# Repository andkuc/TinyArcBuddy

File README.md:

# Tiny Arc Buddy: Embedded STEM Education Platform

An open-source, ATtiny85-based handheld console designed as a dual-purpose platform: a low-level embedded engineering reference and a hands-on STEM educational tool. It is based on the ATtiny85 Tiny Arcade Console by lonesoulsurfer (https://www.instructables.com/Tiny-Arcade-Game-Attiny85).

Developed for STEM workshops, this project aims to demystify hardware assembly and firmware development for 8th-grade middle school students.

---

## 🧠 Pedagogical Approach

The Tiny Arc Buddy is engineered to provide a frictionless, high-impact introduction to STEM for young students without requiring prior programming or electronics experience.

* **Peer-to-Peer Mentoring:** The workshop utilizes a tiered mentoring model. Middle school students act as "Lead Engineers" executing the hands-on work, while older HTL students serve as "Senior Advisors," fostering a collaborative, non-intimidating learning environment.
* **Tangible Milestones:** Hardware assembly is gamified into structural "Levels" (low-profile to high-profile components). This prevents cognitive overload and provides continuous positive reinforcement.
* **Immediate Feedback Loop:** The firmware is structured with a dedicated `ZONE 1: APP SETTINGS`. Students modify straightforward C++ macros (e.g., `#define OWNER_NAME "ANNA"`) and immediately see their changes compiled and rendered on the OLED. This bridges the abstract code-to-hardware gap without bogging them down in syntax errors.
* **Curriculum Alignment:** The software payloads (such as the Affine Linear Function Explorer) directly correlate with the Austrian 8th-grade mathematics and physics curricula, demonstrating the practical application of theoretical school concepts.

---

## ⚡ Hardware Architecture

| **Front Board Layout** | **Schematic Diagram** |
| :---: | :---: |
|  |  |

The hardware is designed around strict BOM constraints, prioritizing low cost, through-hole technology (THT) for beginner soldering, and extreme power efficiency.

* **MCU:** Microchip ATtiny85-20PU (8 KB Flash, 512 Bytes SRAM).
* **Clock:** 8 MHz Internal Oscillator (Fuses must be set; factory 1 MHz will fail I2C timings).
* **Display:** 0.96" I²C SSD1306 Monochrome OLED ($128 \times 64$).
* **Inputs:** * `BTN_LEFT` (PB0) - Direct digital read with internal pull-up.
  * `BTN_RIGHT` (PB2) - Direct digital read with internal pull-up.
  * `BTN_FIRE` (PB5 / ADC0) - Multiplexed via voltage divider (Reset pin constraint).
* **Audio:** Passive Piezo Buzzer driven by PB1.
* **Power:** 3V CR2032 Coin Cell with an SS12F23 slider switch.

> ⚠️ **Hardware Errata / Assembly Note:** > The Piezo Buzzer is routed to PB1 (MISO). Soldering the buzzer *prior* to initial ISP flashing creates signal interference, causing firmware upload failures. The buzzer must be mounted as the final assembly step.

---

## 📑 Bill of Materials (BOM)

| Qty | Component | Designator / Notes |
| :--- | :--- | :--- |
| **1** | Custom PCB | K-Comp / Tiny Arc Buddy revision board |
| **1** | ATtiny85-20PU | Microcontroller (DIP-8 package) |
| **1** | DIL-8 Socket | IC Socket for ATtiny85 |
| **1** | SSD1306 OLED Display | 0.96" I²C Monochrome (128x64) |
| **3** | Resistor 10 kΩ (1%) | Pull-up & voltage divider network |
| **1** | Resistor 68 kΩ (1%) | Battery / Reset line resistor |
| **1** | Resistor 680 Ω (1%) | LED current limiting resistor |
| **3** | Tactile Push Buttons | 6x6 mm Push Buttons (`LEFT`, `RIGHT`, `FIRE`) |
| **1** | Slider Switch | SS12F23 Power Switch |
| **1** | LED 2 mA | Power Indicator Light |
| **1** | CR2032 Battery Holder | **Mount on BOTTOM side of PCB!** |
| **1** | CR2032 3V Battery | Coin Cell Power Source |
| **1** | Passive Piezo Buzzer | **Solder ONLY AFTER programming!** |
| **Tool**| USBasp Programmer | Used for flashing ATtiny85 via DIP-8 socket |

---

## ⚙️ Software Engineering & Memory Optimization

Standard graphics libraries (like Adafruit_SSD1306) require a 1 KB screen buffer, which exceeds the ATtiny85's 512-byte SRAM. The Tiny Arc Buddy firmware bypasses this entirely using custom optimization techniques:

* **Bufferless I²C Rasterization:** The OLED is driven by a custom bit-banged I²C engine (`i2c_start()`, `i2c_write()`). Graphics and text are calculated and pushed to the display pages in real-time, line-by-line, requiring $O(1)$ RAM.
* **Flicker-Free Rendering:** Instead of issuing `oled_clear()` commands, the UI engine employs targeted line-erasure (`clearRestOfLine()`) and fixed-width space padding. This completely eliminates visual artifacts and ghosting during high-frequency loop cycles.
* **Fixed-Point Arithmetic:** To avoid the massive Flash overhead (~1.5 KB) of importing `<math.h>` and utilizing software Floating Point Units (FPU), all physics and geometry calculators use scaled integer math (e.g., storing `3.14` as `314`).
* **PROGMEM Aggregation:** All UI strings, chemical databases, and custom 5x7 compressed hexadecimal font arrays are strictly forced into Flash memory using `pgm_read_byte()` and `pgm_read_word()`.

---

## 📜 Copyright & Licensing

The **Tiny Arc Buddy** is an open educational project developed by Andreas Kucher. To ensure maximum freedom for educators, students, and makers, this repository uses three distinct open-source licenses tailored to different types of content:

### 💻 Software: MIT License
All firmware and source code (`.ino`, `.cpp`, `.h` files) within this repository are released under the **MIT License**.
*Copyright (c) 2026 Andreas Kucher*

You are free to use, copy, modify, merge, publish, distribute, sublicense, and/or sell copies of the software, provided that the original copyright notice and permission notice are included in all copies or substantial portions of the software.

### 🛠️ Hardware: CERN-OHL-P
All hardware design files, including schematics, PCB layouts, and Gerber files, are licensed under the **CERN Open Hardware Licence Version 2 - Permissive (CERN-OHL-P)**. 
You are free to manufacture, modify, and distribute the physical hardware, provided proper attribution is given to the original designers.

### 📖 Documentation: CC BY 4.0
All educational materials, tutorials, and assembly guides (including the *Developer's Handbook*) are licensed under **Creative Commons Attribution 4.0 International (CC BY 4.0)**. 
You are free to share, translate, and adapt the material for any purpose—even commercially—as long as you give appropriate credit to Andreas Kucher.

---

## 🗂️ Repository Structure

```text
.
├── images/
│   ├── Board.png               # PCB component placement & layout render
│   ├── Schematics.png          # Full electronic circuit schematic
├── hardware/
│   ├── TinyArcBuddy.brd        # PCB component placement & layout render
│   ├── TinyArcBuddy1.sch       # Full electronic circuit schematic
│   └── TinyArcBuddy.zip        # Gerber files for PCB manufacturing
├── software/
│   ├── BrickBreaker/           # Brick Breaker Clone
│   ├── LinearFunctions/        # Affine Linear Function Plotter (y = k*x + d)
│   ├── MINTTool/               # SI-Unit aware Math/Physics Engine
│   ├── PeriodicTable/          # 118-Element Relational Database
│   ├── SpaceInvaders/               # Space Invaders
│   ├── TetrisArcade/           # PRNG-driven ATtiny85 Tetris

├── docs/
│   ├── DevelopersGuide.pdf     # Workshop Guide (Student/Tutor Facing)
│   ├── AssortmentBox.pdf       # Kit BOM and assembly order (labels for an assortment box)
│   └── SetupGuide.docx         # Toolchain & driver setup
└── README.md

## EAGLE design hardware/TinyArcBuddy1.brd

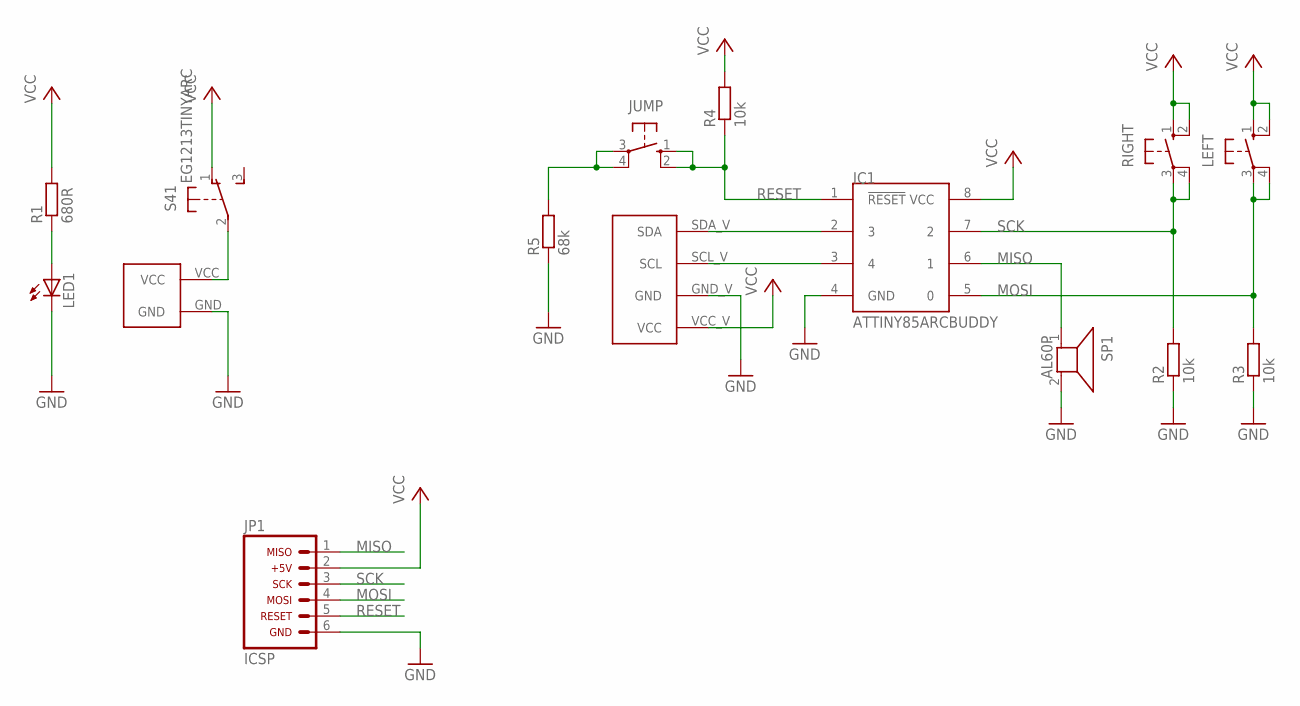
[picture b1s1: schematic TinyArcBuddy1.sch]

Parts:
IC1: ATTINY85ARCBUDDY; DIL08
JP1: ARDUINO_CONN-ICSPTINYARC; CONN-2X03_TINYARC
JUMP: 10-XX; B3F-10XX
LED1: LED3MM
LEFT: 10-XX; B3F-10XX
R1: 680R; 0207/10
R2, R3, R4: 10k; 0207/10
R5: 68k; 0207/10
RIGHT: 10-XX; B3F-10XX
S4: EG1213TINYARC; EG1213_TINYARC
SP1: AL60P
U$1: I2C_OLEDTINYARC; I2C_OLED_PACKAGE_TINYARC
U$2: CR2032; CR2032-20MM

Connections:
GND: IC1.4 (GND), JP1.6, LED1.K (C), R2.1, R3.1, R5.1, SP1.2, U$1.GND_V (GND), U$2.GND
MISO: IC1.6 (1), JP1.1, SP1.1
MOSI: IC1.5 (0), JP1.4, LEFT.3, LEFT.4 (P1), R3.2
unnamed: IC1.3 (4), U$1.SCL_V (SCL)
unnamed: IC1.2 (3), U$1.SDA_V (SDA)
unnamed: S4.2, U$2.VCC
unnamed: LED1.A, R1.1
unnamed: JUMP.3, JUMP.4 (P1), R5.2
RESET: IC1.1 (!RESET), JP1.5, JUMP.1 (S), JUMP.2 (S1), R4.1
SCK: IC1.7 (2), JP1.3, R2.2, RIGHT.3, RIGHT.4 (P1)
VCC: IC1.8 (VCC), JP1.2, LEFT.1 (S), LEFT.2 (S1), R1.2, R4.2, RIGHT.1 (S), RIGHT.2 (S1), S4.1 (O), U$1.VCC_V (VCC)

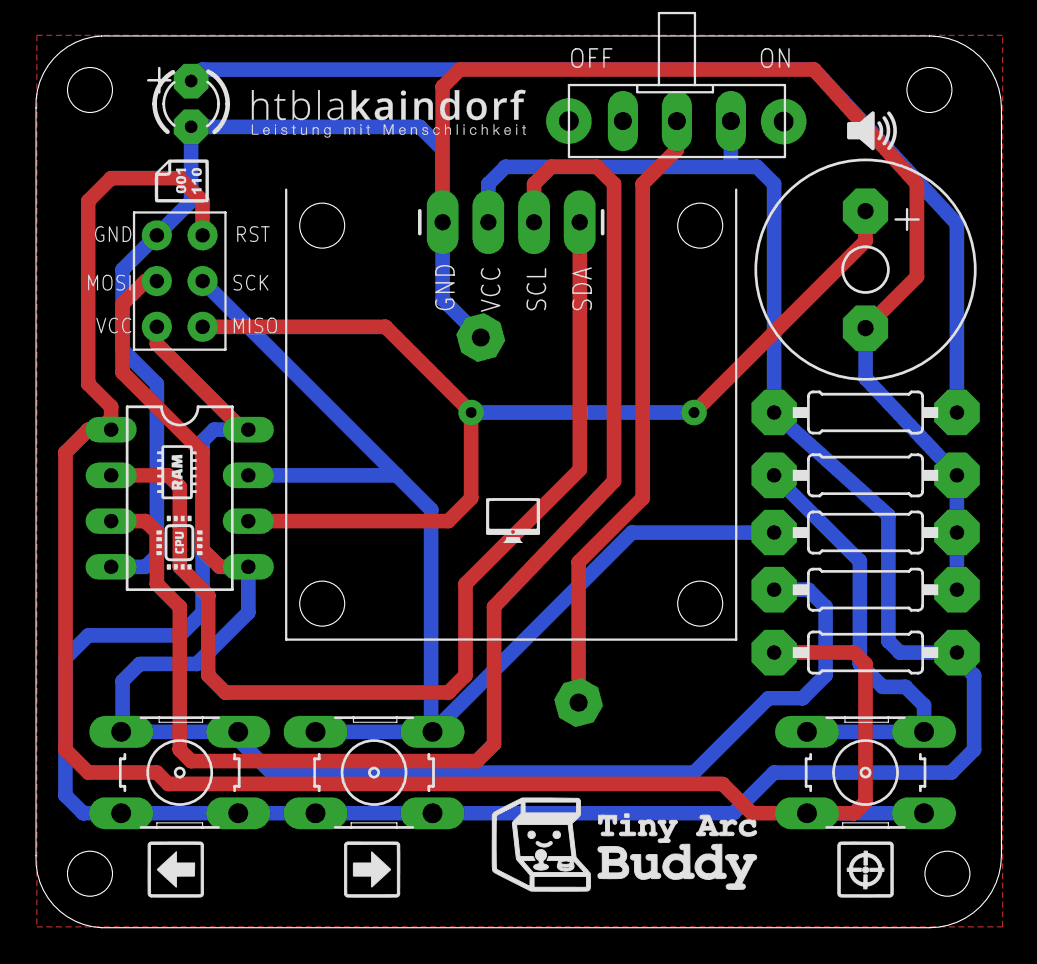
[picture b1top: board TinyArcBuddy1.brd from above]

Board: 2 copper layers, 53.6 x 49.5 mm, 15 parts (1 on the bottom side), 11 nets.
